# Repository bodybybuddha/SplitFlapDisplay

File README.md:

# Split-Flap Display

A modular, 3D-printed split-flap display controllable over RS485 from a Raspberry Pi. Each module holds 64 characters and modules can be chained together to build a display of any width.

**YouTube Build Video:** https://www.youtube.com/watch?v=-C8_AtxEEQc

---

## How It Works

Each module contains:
- A 3D-printed drum that holds 64 individual flaps (one per character)
- A stepper motor driving the drum through a gear train
- A Hall effect sensor for homing
- A custom driver PCB (ATtiny1616 + RS485 transceiver + ULN2003 stepper driver)

Modules communicate over a shared RS485 bus. A Raspberry Pi running a Python web interface sends commands over USB-RS485 to each module individually by address.

---

## Repository Structure

```
CAD/                              - 3D printable parts (Bambu Lab profiles included)
FlapsGenerator/                   - OpenSCAD code to automatically generate (custom) flaps
SplitFlapDriverATtiny1616 V2 KiCad/  - Driver PCB KiCad that I used in the video, for my build
SplitFlapDriverATtiny1616V3       - Updated Driver PCB KiCad project, which should be slightly cheaper to manufacture
SplitFlapBusBoard KiCad/          - Bus board KiCad project
SplitFlapFirmware/                - Arduino firmware for the PCBs
SplitFlap-RPI-FRONTEND/           - Raspberry Pi Python web frontend
Reference Docs/                   - Component datasheets
BOM.md                            - Bill of materials

**OnShape Model:** https://cad.onshape.com/documents/87c916b33ca5d6492b457485/w/b3e5f0f05f6619e6e7931347/e/582ef2164e20b0aa994708ab
```

---

## Parts List

See [BOM.md](BOM.md) for the complete bill of materials, broken into three sections:

- **PCB / Electronics** — all SMD components with JLCPCB part numbers for easy ordering
- **Module BOM** — 3D printed parts and hardware per module, with quantities scaled to 45 modules
- **Other Components** — system-level parts (Raspberry Pi, power supply, C14 connector, etc.)

---

## Ordering the PCB from JLCPCB

The driver board is designed to be ordered from JLCPCB with their PCB Assembly (PCBA) service so the SMD components arrive pre-soldered.

### Step 1 — Export Gerbers from KiCad

1. Open the project in `SplitFlapDriverATtiny1616 V2 KiCad/`
2. In KiCad PCB editor, go to **File → Fabrication Outputs → Gerbers**
3. Export to a folder, then zip the contents
4. Also export the drill file from the same menu

Alternatively, pre-exported Gerber and PCBA files are already be present in the KiCad project folder.

### Step 2 — Upload to JLCPCB

1. Go to [jlcpcb.com](https://jlcpcb.com) and click **Order Now**
2. Upload the Gerber zip file
3. Set your desired quantity (minimum 5)
4. Leave most settings at default; adjust PCB colour if desired

### Step 3 — Enable PCB Assembly (PCBA)

1. Toggle **PCB Assembly** on
2. Select **Standard PCBA** and set the assembly side to **Top Side**
3. Click **Confirm**

### Step 4 — Upload BOM and CPL Files

1. Upload the **BOM file** from the KiCad project folder — this maps component values to JLCPCB part numbers. The part numbers in `BOM.md` match what is in this file.
2. Upload the **CPL (Component Placement List)** file — this tells JLCPCB where each component sits on the board
3. Review the component matches on the next screen. All parts should auto-match using the C-numbers in [BOM.md](BOM.md). Confirm any that need manual review.

### Step 5 — Review and Order

1. Check the parts list — confirm quantities and part numbers match the [BOM.md](BOM.md) PCB section
2. Proceed through the review screens and place your order

> **Note:** A few through-hole parts (pin headers, JST connectors) are not included in PCBA. These are listed in the BOM and will need to be soldered by hand.

---

## 3D Printing

All printable files are in the `CAD/` folder. A Bambu Lab print profile is included in `CAD/64FlapsWithLetters/` for the flaps. Print the flaps in the correct colour for each character — see the video for details on the full 64-character set.

Parts per module:
- Enclosure Body, Right Cover, Left Cover
- Drum Body, Drum Cap
- Motor Gear, Center Gear, Gear Plate
- DIN Rail Mount, Wire Retainer
- 64 Flaps

### Creating your own flaps

If you want to generate your own flaps, with your own font, size and characters, you can use the OpenSCAD script to automatically generate this.

---

## Firmware

Located in `SplitFlapFirmware/`. The firmware is Arduino-based and targets the ATtiny1616.

- Flash via UPDI programmer (see https://github.com/SpenceKonde/AVR-Guidance/blob/master/UPDI/jtag2updi.md if you need to make one)
- Each module needs a unique address (0–44) stored in EEPROM. Be sure to edit this between flashes.

---

## Frontend

Located in `SplitFlap-RPI-FRONTEND/`. A Python web interface running on a Raspberry Pi sends display commands over USB-RS485 at 115200 baud.

Need a USB-serial dongle. I used this one: https://www.adafruit.com/product/5994

---

## License

This project is licensed under [Creative Commons Attribution-NonCommercial-ShareAlike 4.0 International (CC BY-NC-SA 4.0)](https://creativecommons.org/licenses/by-nc-sa/4.0/).

You are free to share and adapt this project for non-commercial purposes, as long as you give appropriate credit to Adam G Makes and distribute any derivatives under the same license.

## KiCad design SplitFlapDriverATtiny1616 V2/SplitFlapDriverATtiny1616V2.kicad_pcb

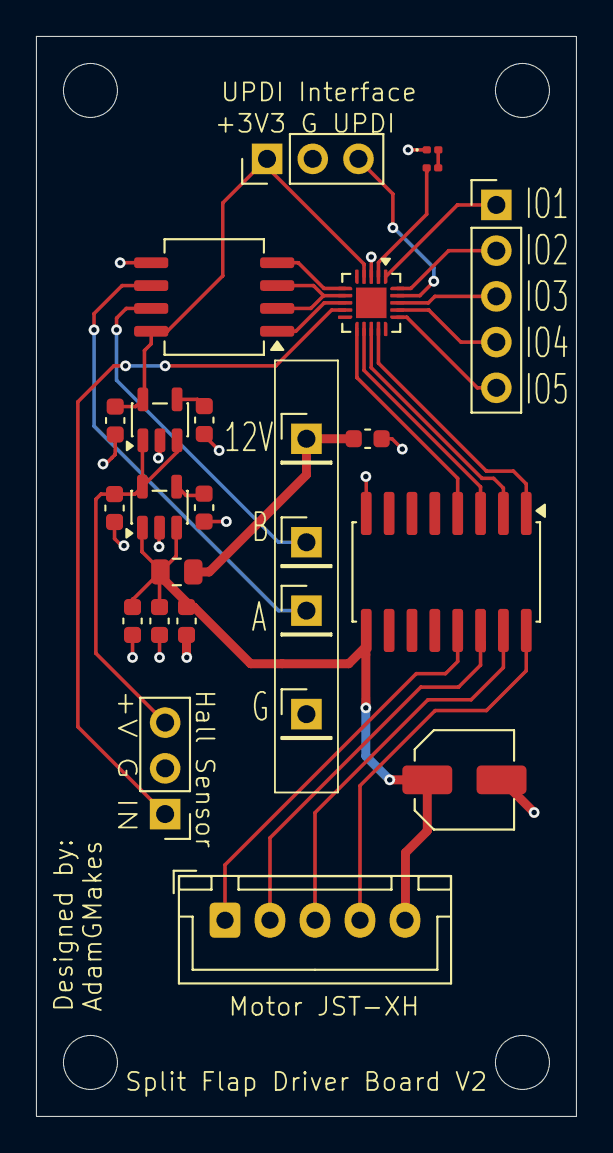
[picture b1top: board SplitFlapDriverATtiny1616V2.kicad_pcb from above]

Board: 2 copper layers, 30.0 x 60.0 mm, 25 parts (0 on the bottom side), 29 nets.

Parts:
C1: 100u; C_Elec_5x5.4
C2, C3, C6, C8: 470n; C_0603_1608Metric
C4, C5, C9: 10u; C_0603_1608Metric
C7: 100n; C_0603_1608Metric
D1: LED; LED_0201_0603Metric
J1: UPDI Programming; PinHeader_1x03_P2.54mm_Vertical
J2, J6, J7, J8: Conn_01x01_Pin; PinHeader_1x01_P2.54mm_Vertical
J3: Stepper Connector; JST_XH_B5B-XH-A_1x05_P2.50mm_Vertical
J4: Hall Effect; PinHeader_1x03_P2.54mm_Vertical
J5: Conn_01x05_Pin; PinHeader_1x05_P2.54mm_Vertical
R1: 0R; R_0805_2012Metric
R2: 60R; R_0201_0603Metric
U1: ATtiny1616-MNR; VQFN-20-1EP_3x3mm_P0.4mm_EP1.7x1.7mm
U2: ULN2003ADR; SOIC-16W_5.3x10.2mm_P1.27mm
U3: SN65HVD72DR; SOIC-8_5.3x6.2mm_P1.27mm
U5: SPX3819M5-L-3-3; SOT-23-5
U6: SPX3819M5-L-5-0; SOT-23-5

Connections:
+3V3: C5.1, J1.1, U1.4 (VCC), U3.8 (VCC), U5.5 (OUT)
+5V: C9.1, J4.3, U5.1 (IN), U5.3 (EN), U6.5 (OUT)
+VBUS: C2.1, J2.1, R1.1
+VBUSF: C1.1, C3.1, C4.1, C7.1, J3.5, R1.2, U2.9 (COM), U6.1 (IN), U6.3 (EN)
DE/RE: U1.7 (PA6), U3.2 (~RE), U3.3 (DE)
GND: C1.2, C2.2, C3.2, C4.2, C5.2, C6.2, C7.2, C8.2, C9.2, D1.1 (K), J1.2, J4.2, J6.1, U1.3 (GND), U2.8 (GND), U3.5 (GND), U5.2 (GND), U6.2 (GND)
HALL_IN: J4.1, U1.9 (PB5)
IO1: J5.1, U1.1 (PA2)
IO2: J5.2, U1.20 (PA1)
IO3: J5.3, U1.18 (PC3)
IO4: J5.4, U1.17 (PC2)
IO5: J5.5, U1.16 (PC1)
M1: J3.4, U2.16 (O1)
M2: J3.3, U2.15 (O2)
M3: J3.2, U2.14 (O3)
M4: J3.1, U2.13 (O4)
unnamed: D1.2 (A), R2.1
unnamed: C6.1, U5.4 (BP)
unnamed: C8.1, U6.4 (BP)
RS465_A: J8.1, U3.6 (A)
RS465_B: J7.1, U3.7 (B)
RXD: U1.8 (PA7), U3.1 (R)
STATUS_LED: R2.2, U1.2 (EXTCLK/PA3)
TXD: U1.6 (PA5), U3.4 (D)
ULN_IN1: U1.14 (PB0), U2.1 (I1)
ULN_IN2: U1.13 (PB1), U2.2 (I2)
ULN_IN3: U1.12 (PB2/TOSC2), U2.3 (I3)
ULN_IN4: U1.11 (PB3/TOSC1), U2.4 (I4)
UPDI: J1.3, U1.19 (~RESET/PA0/UPDI)

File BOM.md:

# Split-Flap Display BOM (Bill of Materials)

## Project Overview
A modular split-flap display system with 64 characters per module, controllable via RS485 from a Raspberry Pi. Designed by Adam G Makes.

**YouTube Video:** https://www.youtube.com/watch?v=-C8_AtxEEQc

**YouTube Channel:** https://www.youtube.com/@AdamGMakes

---

## PCB / Electronics BOM (Per Driver Board)

| Comment | Designator | Footprint | JLCPCB Part # |
|---------|-----------|-----------|---------------|
| ATtiny1616-MNR | U1 | VQFN-20-1EP_3x3mm_P0.4mm_EP1.7x1.7mm | C507118 |
| 470n | C3, C8, C6, C2 | C_0603_1608Metric | C1623 |
| ULN2003ADR | U2 | SOIC-16W_5.3x10.2mm_P1.27mm | C7512 |
| HallEffect | J4 | PinHeader_1x03_P2.54mm_Vertical | C131339 |
| 100u | C1 | C_Elec_5x5.4 | C3347 |
| 100n | C7 | C_0603_1608Metric | C14663 |
| **0R** | R1 | R_0805_2012Metric | C17477 |
| LED | D1 | LED_0201_0603Metric | C3646923 |
| StepperConnector | J3 | JST_XH_B5B-XH-A_1x05_P2.50mm_Vertical | C157991 |
| SN65HVD72DR | U3 | SOIC-8_5.3x6.2mm_P1.27mm | C48125 |
| 60R | R2 | R_0201_0603Metric | C88957 |
| SPX3819M5-L-3-3 | U5 | SOT-23-5 | C20617301 |
| SPX3819M5-L-5-0 | U6 | SOT-23-5 | C20617302 |
| 10u | C5, C9, C4 | C_0603_1608Metric | C19702 |

Note: R1 is a 0 Ohm resistor.
---

## Module BOM

### 3D Printed Parts

| Part | Qty per Module | Qty (45 Modules) |
|------|---------------|-----------------|
| Enclosure Body | 1 | 45 |
| Enclosure Right Cover | 1 | 45 |
| Enclosure Left Cover | 1 | 45 |
| Drum Body | 1 | 45 |
| Drum Cap | 1 | 45 |
| DIN Rail Mount | 1 | 45 |
| Motor Gear | 1 | 45 |
| Center Gear | 1 | 45 |
| Gear Plate | 1 | 45 |
| Wire Retainer | 1 | 45 |
| Flap | 64 | 2880 |

### Other Parts

| Part | Qty per Module | Qty (45 Modules) |
|------|---------------|-----------------|
| M3 Nuts | 12 | 540 |
| M3 x 8mm Flat Head Screw | 4 | 180 |
| M3 x 30mm Flat Head Screw | 4 | 180 |
| M3 x 40mm Flat Head Screw | 4 | 180 |
| A3144 Hall Effect Sensor | 1 | 45 |
| **28BYJ-48 12V Stepper Motor**| 1 | 45 |
| Driver Board | 1 | 45 |
| Pogo Pins *1 | 4 | 180 |
| 3x1mm N52 Magnet | 1 | 45 |
| 3-Pin JST Connector | 1 | 45 |

*1 -  Pogo Pin: total length 9mm needle head 2.0mm tube length 5.0mm tail length 2.0mm tail diameter 1.0mm (https://a.co/d/0a69mnW1)

Note: Keep in mind, the driver boards are designed to be used with 12V motors, not the common 5V variety.

---

## Other Components (System-Level)

| Qty | Component | Notes |
|-----|-----------|-------|
| 1 | Raspberry Pi | Controller |
| 1 | USB-RS485 Dongle | PC/RPi to RS485 adapter |
| 1 | 12V Power Supply | Module power |
| 1 | C14 Power Connector | Panel-mount inlet |
| 1 | Power Switch | Main power switch |
| 1 | C14 Power Cable | IEC mains cable |

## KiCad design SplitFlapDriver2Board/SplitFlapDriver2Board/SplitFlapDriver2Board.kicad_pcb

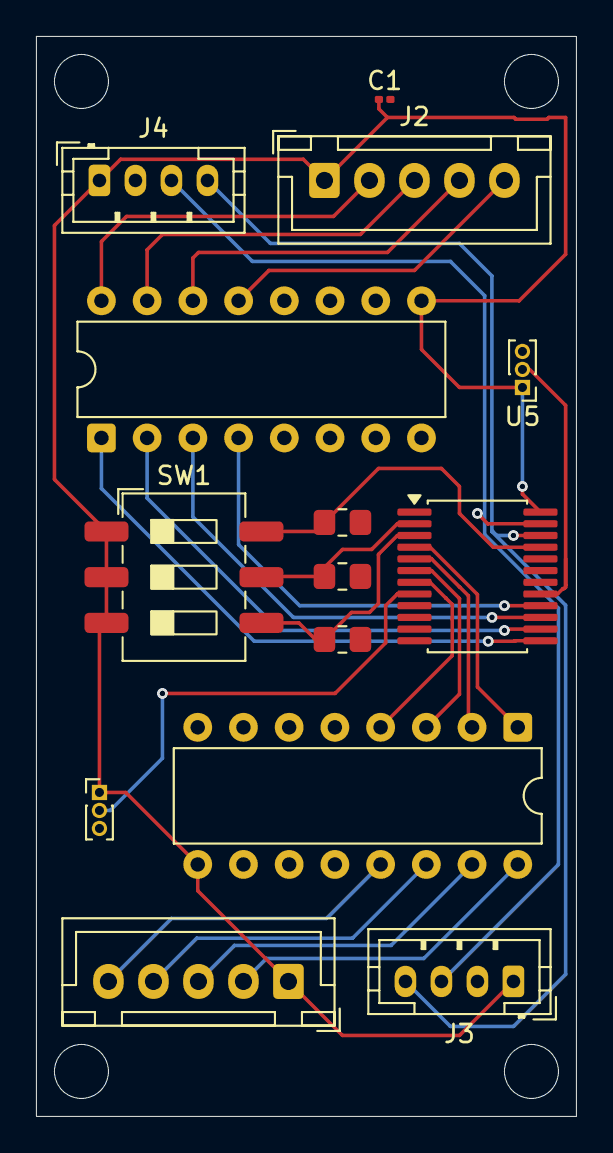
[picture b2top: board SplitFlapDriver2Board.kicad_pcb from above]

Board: 2 copper layers, 30.0 x 60.0 mm, 14 parts (0 on the bottom side), 25 nets.

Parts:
C1: C_Polarized; C_0201_0603Metric
J1, J2: Conn_01x05_Socket; JST_XH_B5B-XH-A_1x05_P2.50mm_Vertical
J3: Conn_01x04_Socket; JST_PH_B4B-PH-K_1x04_P2.00mm_Vertical
J4: Conn_01x04_Pin; JST_PH_B4B-PH-K_1x04_P2.00mm_Vertical
R1, R2, R3: 9.1K; R_0805_2012Metric_Pad1.20x1.40mm_HandSolder
SW1: SW_DIP_x03; SW_DIP_SPSTx03_Slide_6.7x9.18mm_W8.61mm_P2.54mm_LowProfile
U1: PCF8575DBR; SSOP-24_5.3x8.2mm_P0.65mm
U2, U3: ULN2003A; DIP-16_W7.62mm
U4, U5: A1104xLH; PinHeader_1x03_P1.00mm_Vertical

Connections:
+5V: C1.1, J1.1, J2.1, J3.1, J4.1, SW1.1, SW1.2, SW1.3, U1.24 (VCC), U2.9 (COM), U3.9 (COM), U4.1 (V_{CC}), U5.1 (V_{CC})
GND: C1.2, J3.2, J4.2, R1.2, R2.2, R3.2, U1.12 (GND), U2.8 (GND), U3.8 (GND), U4.3 (GND), U5.3 (GND)
unnamed: J1.2, U2.16 (O1)
unnamed: J1.3, U2.15 (O2)
unnamed: J1.4, U2.14 (O3)
unnamed: J1.5, U2.13 (O4)
unnamed: J2.2, U3.16 (O1)
unnamed: J2.3, U3.15 (O2)
unnamed: J2.4, U3.14 (O3)
unnamed: J2.5, U3.13 (O4)
unnamed: R3.1, SW1.6, U1.21 (A0)
unnamed: R2.1, SW1.5, U1.2 (A1)
unnamed: R1.1, SW1.4, U1.3 (A2)
unnamed: U1.4 (P0), U2.1 (I1)
unnamed: U1.5 (P1), U2.2 (I2)
unnamed: U1.6 (P2), U2.3 (I3)
unnamed: U1.7 (P3), U2.4 (I4)
unnamed: U1.8 (P4), U4.2 (V_{OUT})
unnamed: U1.13 (P10), U3.1 (I1)
unnamed: U1.14 (P11), U3.2 (I2)
unnamed: U1.15 (P12), U3.3 (I3)
unnamed: U1.16 (P13), U3.4 (I4)
unnamed: U1.17 (P14), U5.2 (V_{OUT})
SCL: J3.4, J4.4, U1.22 (SCL)
SDA: J3.3, J4.3, U1.23 (SDA)

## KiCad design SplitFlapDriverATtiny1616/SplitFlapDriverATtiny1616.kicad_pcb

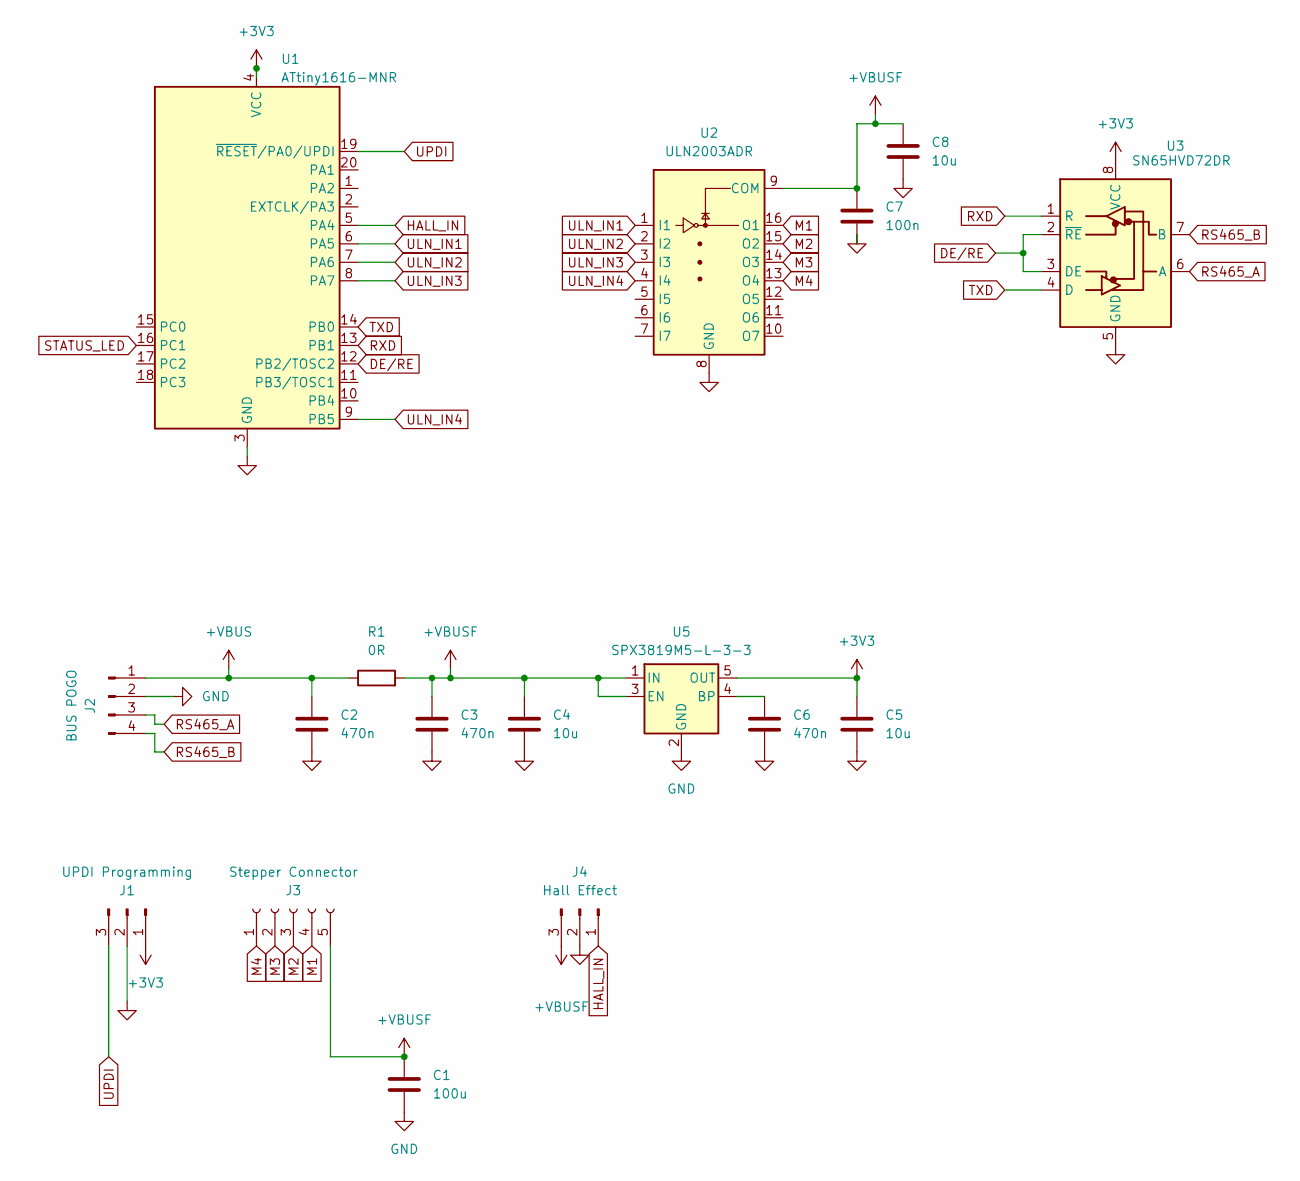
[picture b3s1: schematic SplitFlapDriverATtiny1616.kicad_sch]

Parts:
C1: 100u; C_Elec_5x5.4
C2, C3, C6: 470n; C_0603_1608Metric
C4, C5, C8: 10u; C_0603_1608Metric
C7: 100n; C_0603_1608Metric
J1: UPDI Programming; PinHeader_1x03_P2.54mm_Vertical
J2: BUS POGO; PinHeader_1x04_P2.54mm_Vertical
J3: Stepper Connector; JST_XH_B5B-XH-A_1x05_P2.50mm_Vertical
J4: Hall Effect; PinHeader_1x03_P2.54mm_Vertical
R1: 0R; R_0805_2012Metric
U1: ATtiny1616-MNR; VQFN-20-1EP_3x3mm_P0.4mm_EP1.7x1.7mm; Manufacturer Part Number ATTINY1616-MNR; JLCPCB Part Number C507118
U2: ULN2003ADR; SOIC-16W_5.3x10.2mm_P1.27mm; Manufacturer Part Number ULN2003ADR; JLCPCB Part Number C7512
U3: SN65HVD72DR; SOIC-8_5.3x6.2mm_P1.27mm; Manufacturer Part Number SN65HVD72DR; JLCPCB Part Number C48125
U5: SPX3819M5-L-3-3; SOT-23-5

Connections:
+3V3: C5.1, J1.1, U1.4 (VCC), U3.8 (VCC), U5.5 (OUT)
+VBUS: C2.1, J2.1, R1.1
+VBUSF: C1.1, C3.1, C4.1, C7.1, C8.1, J3.5, J4.3, R1.2, U2.9 (COM), U5.1 (IN), U5.3 (EN)
DE/RE: U1.12 (PB2/TOSC2), U3.2 (~RE), U3.3 (DE)
GND: C1.2, C2.2, C3.2, C4.2, C5.2, C6.2, C7.2, C8.2, J1.2, J2.2, J4.2, U1.3 (GND), U2.8 (GND), U3.5 (GND), U5.2 (GND)
HALL_IN: J4.1, U1.5 (PA4)
M1: J3.4, U2.16 (O1)
M2: J3.3, U2.15 (O2)
M3: J3.2, U2.14 (O3)
M4: J3.1, U2.13 (O4)
unnamed: C6.1, U5.4 (BP)
RS465_A: J2.3, U3.6 (A)
RS465_B: J2.4, U3.7 (B)
RXD: U1.13 (PB1), U3.1 (R)
STATUS_LED: U1.16 (PC1)
TXD: U1.14 (PB0), U3.4 (D)
ULN_IN1: U1.6 (PA5), U2.1 (I1)
ULN_IN2: U1.7 (PA6), U2.2 (I2)
ULN_IN3: U1.8 (PA7), U2.3 (I3)
ULN_IN4: U1.9 (PB5), U2.4 (I4)
UPDI: J1.3, U1.19 (~RESET/PA0/UPDI)

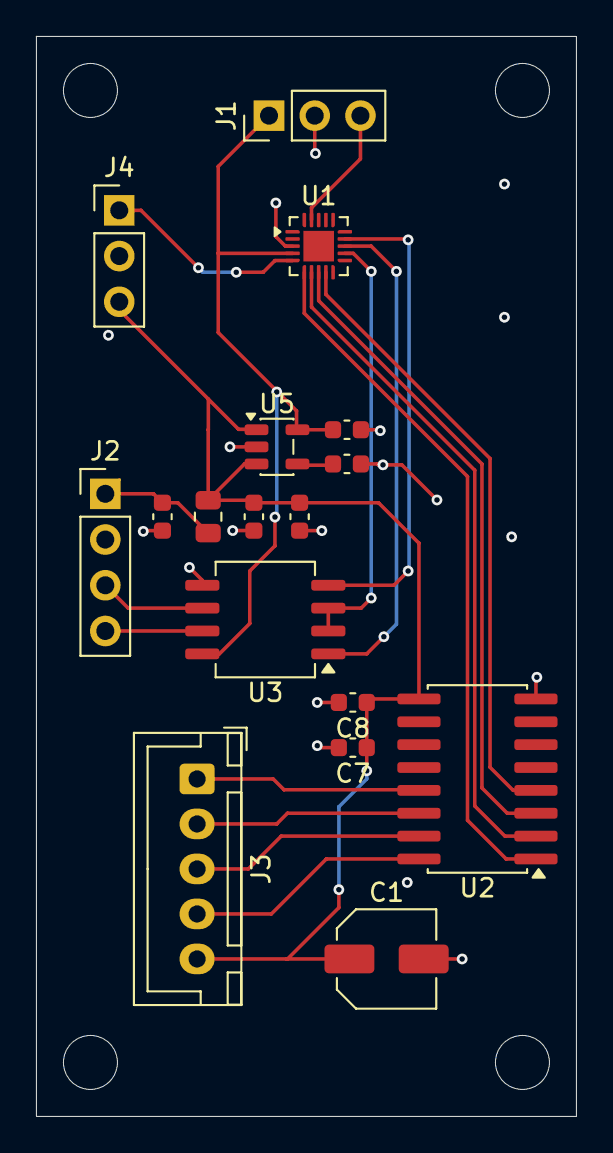
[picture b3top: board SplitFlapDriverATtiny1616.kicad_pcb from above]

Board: 2 copper layers, 30.0 x 60.0 mm, 17 parts (0 on the bottom side), 20 nets.

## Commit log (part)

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2025-11-13 New KiCad Project for SplitFlapDriverATtiny1616
2025-11-17 Added SplitFlapBusBoard
2025-12-05 Version 2 of Hub and Module Board
    Finished and ordered bus board and V2 or Module board (50x)
2026-02-24 added firmware and python frontend code
2026-02-24 updated firmware
2026-04-25 added wire retainer
2026-04-27 Delete SplitFlapDriverATtiny1616 V2.zip
    removed incorrect fab files
2026-04-27 Updated BOM and CPL files to work better in JLCPCB
2026-04-27 Updated folder name for clarity
2026-04-27 updated BOM and CPL files to work better with JLCPCB
2026-04-27 Added V3 Splitflap PCB
    Contains updated footprint for D1 and R2, which don't require Standard PCB assembly and can use Economic PCBA instead, saving money
2026-05-04 Added flaps auto generator
2026-05-04 Added flaps automatic generator
2026-05-04 Added Ypos adjustment and Size adjustement per char
2026-05-04 added pogo pin details
